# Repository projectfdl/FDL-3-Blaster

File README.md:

# FDL-3-Blaster

Welcome to the FDL-3 blaster repository

## This project is licensed under the terms of the Creative Commons Non-Commercial Attribution Share Alike 4.0 license
Print it, tweak it, share it and if you do and give us props. Please don't sell it without Project FDL permission.

<br>
<br>

# Operating your FDL-3

## Settings (Applicable to full auto tail, firmware version 1.05)

**Speed**<br>
Value: 0 - 100 : Default: 50<br>
Speed or power setting used to adjust the velocity the blaster fires darts.<br><br>

**ROF (Rate of Fire)**<br>
Value: 0 - 100 : Default: 100<br>
Rate of fire setting to adjust time between each dart fired when in burst or full auto.<br><br>

**Burst**<br>
Value: 1, 2, 3, F : Default: 1<br>
Number of darts fired per single trigger pull. F (full auto) will continue firing darts until you release the trigger.<br><br>

**MinSpin (Minimum Spinup)**<br>
Value: 120 - 500 : Default: 220<br>
Time in milliseconds for motors to spinup between trigger pull and firing dart when speed set to 0.<br><br>

**MaxSpin (Maximum Spinup)**<br>
Value: 150 - 500 : Default: 200<br>
Time in milliseconds for motors to spinup between trigger pull and firing dart when speed set to 100.
Note: MinSpin and MaxSpin together create a range of spinup time. When speed is set to 50, spinup time is half way between MinSpin and MaxSpin. Eg. MinSpin = 200, MaxSpin = 300, Speed = 50. Actual spinup time = 250. Speed = 75. Actual spinup time = 275.<br><br>

**Fire Mode**<br>
Value: SAFE, ABIDE, AUTO, CACHE : Default: ABIDE<br>
Setting for how the blaster reacts to a trigger pull prior to firing a dart.<br>
- Safe: safety mode. Blaster will beep and not fire dart.
- Abide: Trigger abide. Blaster will only fire a dart if trigger is held down for the full spinup duration. If trigger is released prior to the completion of spinupt time, the blaster will not fire.
- Auto: Blaster will fire dart automatically. If trigger is released prior to the completion of spinup time, the blaster will continue it's fire cycle and proceed to fire all darts set by the burst setting.
- Cache: Cached mode. The blaster will "cache" the number of trigger pulls during the spinup duration. If you are able to pull the trigger three times during spinup, the blaster will fire three darts. Twice, two darts. Once, one dart.<br><br>

**Spindown**<br>
Value: 7 - 18 : Default: 14<br>
Rate at which the blasters motors wind down or "spindown" to a stop. Lower is faster. Higher is slower. The value is technically equal to the time in milliseconds to lower the speed of the blaster by a single increment.<br><br>

**Idle (Idle Time)**<br>
Value: 0 - 10 : Default: 0<br>
After the end of a fire cycle the motors will spin at a slow idle speed for this number of seconds. This allows the motors to spinup faster than if they were to start from a dead stop. Setting this to 0 will disable the feature. Note: if the trigger is held down at the end of a fire cycle, the motors will run at this idle speed until trigger is released.<br><br>

**Load**<br>
Load user preset 1, 2, 3 or back out of menu.<br><br>

**Save**<br>
Save current blaster settings to one of three user preset slots which can be recalled later by the load menu or user buttons on the side of the blaster. Note: only settings prior before the Load menu item are stored in presets. Speed, ROF, Burst, MinSpin, MaxSpin, FireMode, Spindown and Idle.<br><br>

**MinSpd (Minimum Speed)**<br>
Value: 0 - 100 : Default: 0<br>
Determines the minimum speed value that may be set by the speed setting. Eg. if set to 25, the speed gauge will not go lower than 25.<br><br>

**MaxSpd (Maximum Speed)**<br>
Value: 0 - 100 : Default: 100<br>
Determines the maximum speed value that may be set by the speed setting. Eg. if set to 80, the speed gauge will not go higher than 80. Recalled presets with higher speed values will default to this setting. The last value this setting was set to prior to powering off the blaster can be locked by flipping the red speed lock switch located on next to the screen on the board in the rear of the blaster. The rear cap piece must be removed to access this switch. This value cannot be altered while the blaster speed lock is enabled.<br><br>

**BtnMode (Button Mode)**<br>
Value: PRESET, SPEED, ROF, BURST : Default: BURST<br>
Determines what the three user quick buttons on the side of the blaster do. These buttons must be briefly held down for action to take place.<br>
- Preset: Loads user preset. Front button loads preset 1. Rear button closed to user loads preset 3.
- Speed: Sets blaster speed. From front to rear button. 50, 75, 100
- ROF: Set blaster rate of fire. From front to rear button. 50, 75, 100
- Burst: Sets blaster burst count. From front to rear button. 1, 2, F<br><br>

**BrkAgr (Braking Aggression)**<br>
Value: 3 - 20 : Default: 16<br>
Determines how aggressively the pusher brakes prior to reaching a stop at the rear of its cycle. Setting lower may produce a more responsive cycle but may leave the pusher extended at the end of the cycle. Setting higher may resolve issues with a pusher that does not stop properly at the rear of its cycle. This setting should rarely need to change.<br><br>

**ULock (User Lock)**<br>
Enable complete blaster lockout by setting a user defined sequence of quick button presses. Blaster will not function once lock is set and may be unlocked by reentering the defined sequence. Note: do not forget your code. While it is possible to reset your blaster, the method of doing so is not described in this document.<br><br>

**Bright (Brightness)**<br>
Value: 0 - 100 : Default: 100<br>
Sets the brightness of the oled display. This is a very subtle change in a high light environment but more obvious in darker surroundings.<br><br>

**Sound**<br>
Value: OFF, ON : Default: ON<br>
Enables or disables audible beeping while navigating menus, loading presets etc.<br><br>

**BatOff (Battery Offset)**<br>
Value: -5 - 5 : Default: 0<br>
Offsets the read battery voltage in increments of 0.1 volts. This is only for use with legacy or self built blasters if a full 3s battery does not read 12.6 volts.<br><br>

**Info**<br>
Displays current firmware version.<br><br>

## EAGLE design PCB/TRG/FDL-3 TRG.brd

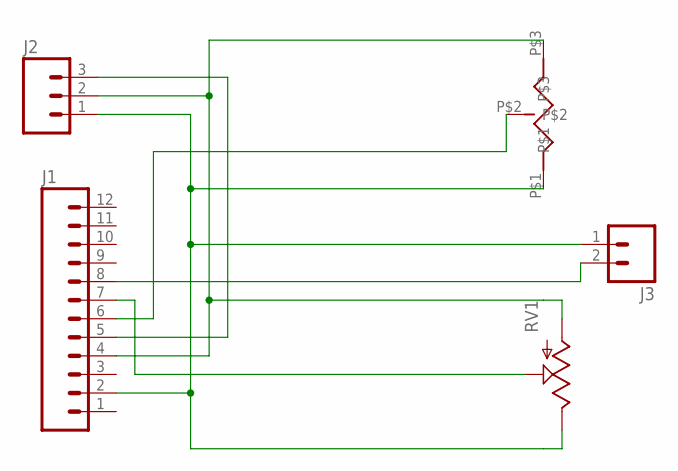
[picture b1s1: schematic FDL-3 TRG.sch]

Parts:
J1: M12LONGPADS; 1X12_LONGPADS
J2: M03LONGPADS; 1X03_LONGPADS
J3: M02PTH3; 1X02_LONGPADS
RV1: POTTRIM; TRIM_POT
U$1: THRUHOLEPOT

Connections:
unnamed: J1.2, J2.1, J3.1, RV1.2 (E), U$1.P$1
unnamed: J1.4, J2.2, RV1.3 (A), U$1.P$3
unnamed: J1.5, J2.3
unnamed: J1.6, U$1.P$2
unnamed: J1.7, RV1.1 (S)
unnamed: J1.8, J3.2

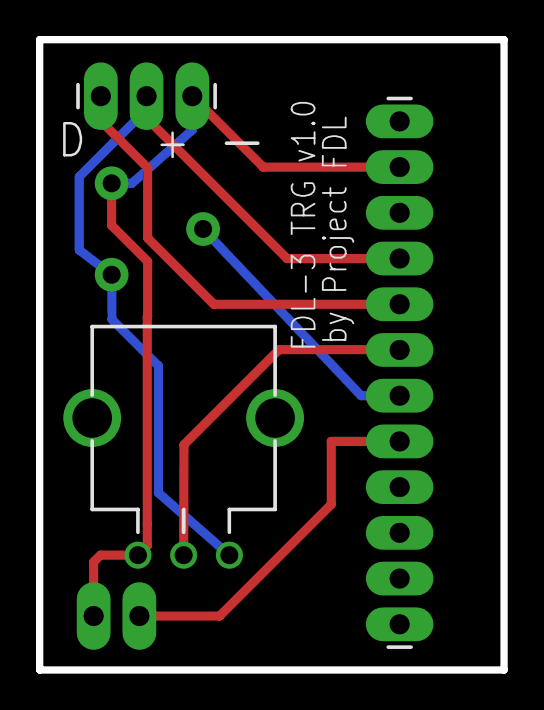
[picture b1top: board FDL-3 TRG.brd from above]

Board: 2 copper layers, 25.8 x 35.0 mm, 5 parts (0 on the bottom side), 6 nets.

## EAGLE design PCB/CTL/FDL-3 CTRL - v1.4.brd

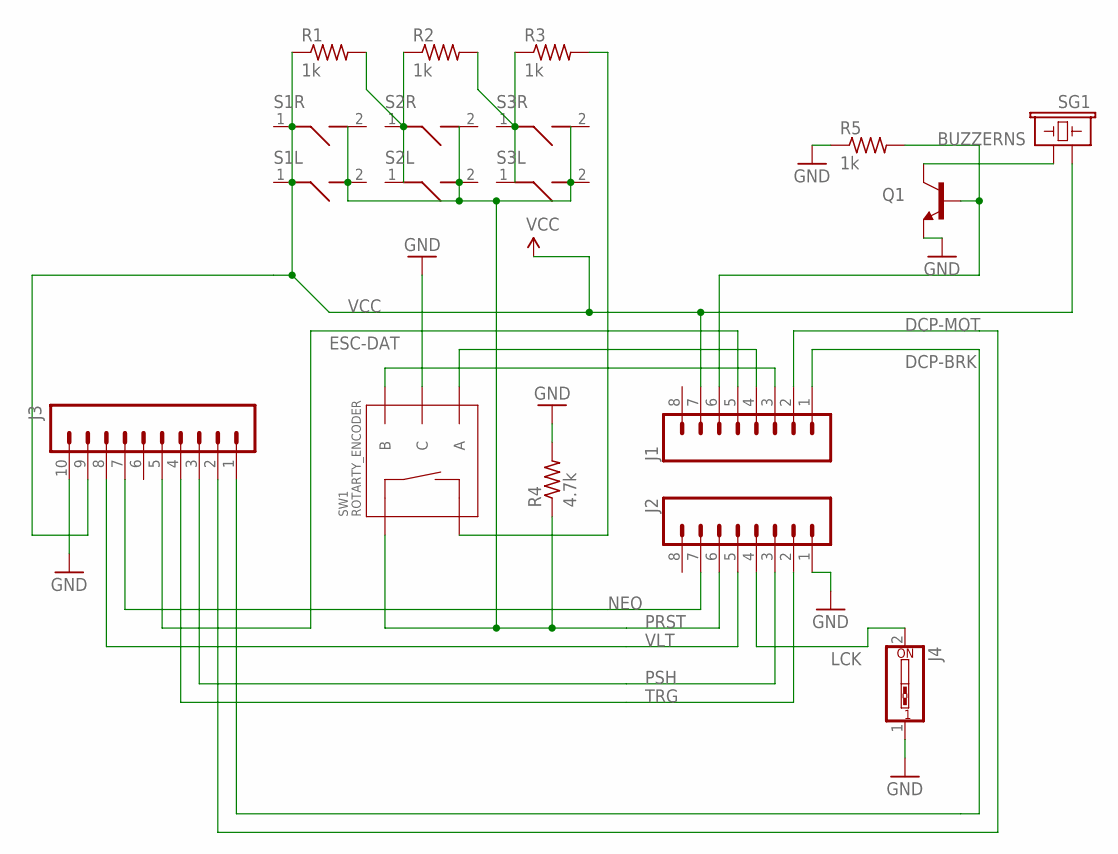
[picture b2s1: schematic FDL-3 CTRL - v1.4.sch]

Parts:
J1, J2: M08SILK_FEMALE_PTH; 1X08
J3: M10SILK_FEMALE_PTH; 1X10
J4: SW_DIP-1; EDG-01
Q1: TRANSISTOR_NPNBC547; TO-92-AMMO
R1, R2, R3, R5: 1k; 0204/5
R4: 4.7k; 0204/5
S1L, S1R, S2L, S2R, S3L, S3R: RGTANGTCTBTN
SG1: BUZZERNS; BUZZER-12MM-NS
SW1: ROTARTY_ENCODER; ROTARY_ENC_PLAIN

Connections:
DCP-BRK: J1.1, J3.1
DCP-MOT: J1.2, J3.2
ESC-DAT: J1.5, J3.5
GND: J2.1, J3.10, J4.1, Q1.3 (E), R4.2, R5.1, SW1.C
LCK: J2.4, J4.2
unnamed: R1.2, R2.1, S2L.1, S2R.1
unnamed: R2.2, R3.1, S3L.1, S3R.1
unnamed: R3.2, SW1.SW-
unnamed: Q1.1 (C), SG1.- (2)
unnamed: J1.4, SW1.A
unnamed: J1.3, SW1.B
unnamed: J1.6, Q1.2 (B), R5.2
NEO: J2.7, J3.7
PRST: J2.6, R4.1, S1L.2, S1R.2, S2L.2, S2R.2, S3L.2, S3R.2, SW1.SW+
PSH: J2.3, J3.3
TRG: J2.2, J3.4
VCC: J1.7, J3.9, R1.1, S1L.1, S1R.1, SG1.+ (1)
VLT: J2.5, J3.8

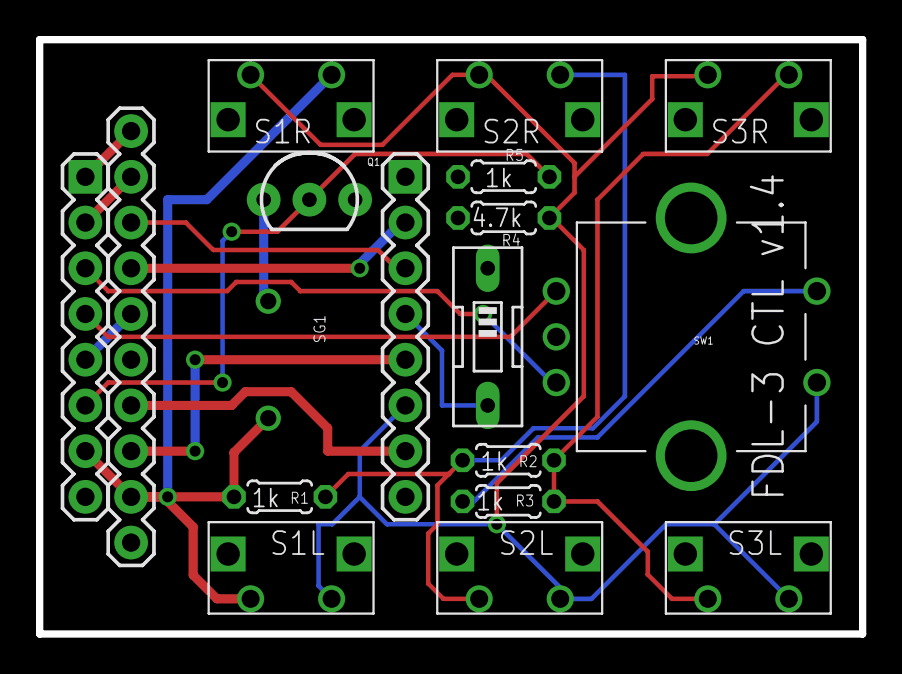
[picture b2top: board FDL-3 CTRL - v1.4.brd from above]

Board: 2 copper layers, 45.7 x 33.0 mm, 18 parts (0 on the bottom side), 18 nets.

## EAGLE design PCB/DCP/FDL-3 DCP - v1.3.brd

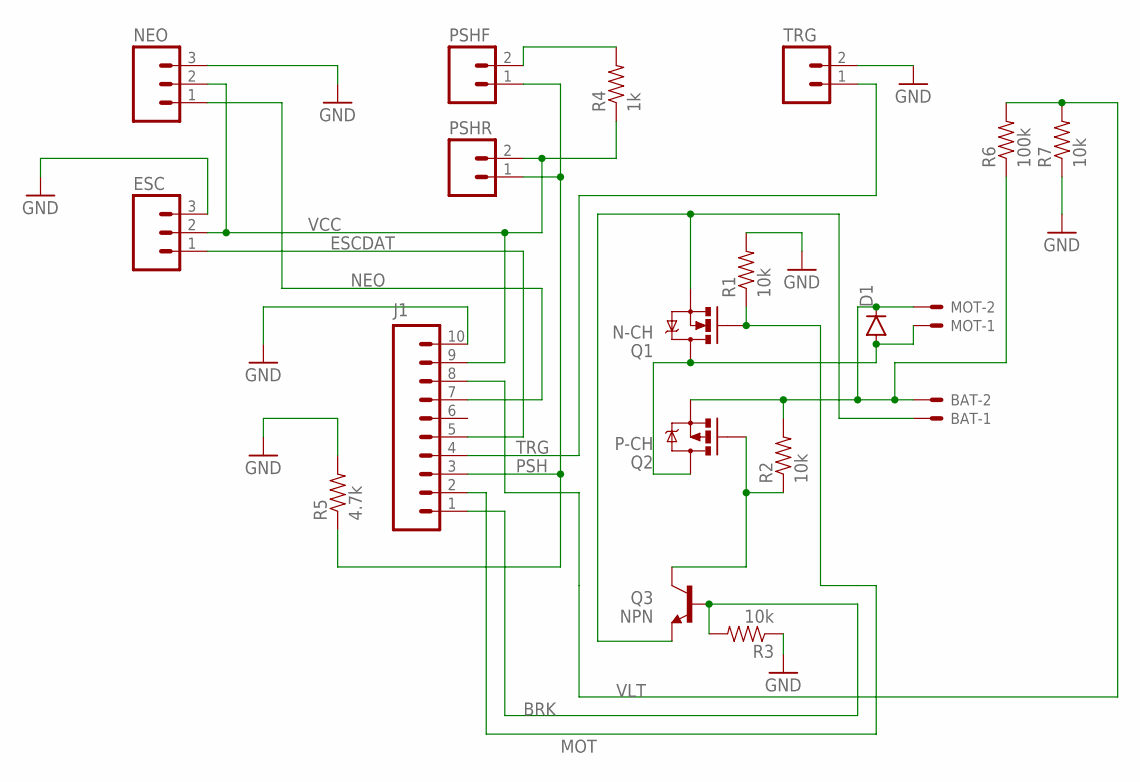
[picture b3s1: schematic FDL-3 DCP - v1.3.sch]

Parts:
BAT: JST-XH-02-PIN-LONG-PAD; JST-XH-02-PACKAGE-LONG-PAD
D1: DIODEPTH; DIODE-1N4001
ESC: M03PTH; 1X03
J1: M10SILK_FEMALE_PTH; 1X10
MOT: JST-XH-02-PIN-LONG-PAD; JST-XH-02-PACKAGE-LONG-PAD
NEO: M03PTH; 1X03
PSHF: M02PTH; 1X02
PSHR: M02PTH; 1X02
Q1: N-CH; TO220V
Q2: P-CH; TO220V
Q3: NPN; TO-92
R1, R2, R3, R7: 10k; AXIAL-0.3EZ
R4: 1k; AXIAL-0.3EZ
R5: 4.7k; AXIAL-0.3EZ
R6: 100k; AXIAL-0.3EZ
TRG: M02PTH; 1X02

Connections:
BRK: J1.1, Q3.2 (B), R3.P$2 (2)
ESCDAT: ESC.1, J1.5
GND: BAT.1, ESC.3, J1.10, NEO.3, Q1.3 (S), Q3.1 (E), R1.P$2 (2), R3.P$1 (1), R5.P$2 (2), R7.P$1 (1), TRG.2
MOT: J1.2, Q1.1 (G), R1.P$1 (1)
unnamed: Q2.1 (G), Q3.3 (C), R2.P$1 (1)
unnamed: BAT.2, D1.C, MOT.2, Q2.3 (S), R2.P$2 (2), R6.P$1 (1)
unnamed: D1.A, MOT.1, Q1.2 (D), Q2.2 (D)
unnamed: PSHF.2, R4.P$2 (2)
NEO: J1.7, NEO.1
PSH: J1.3, PSHF.1, PSHR.1, R5.P$1 (1)
TRG: J1.4, TRG.1
VCC: ESC.2, J1.9, NEO.2, PSHR.2, R4.P$1 (1)
VLT: J1.8, R6.P$2 (2), R7.P$2 (2)

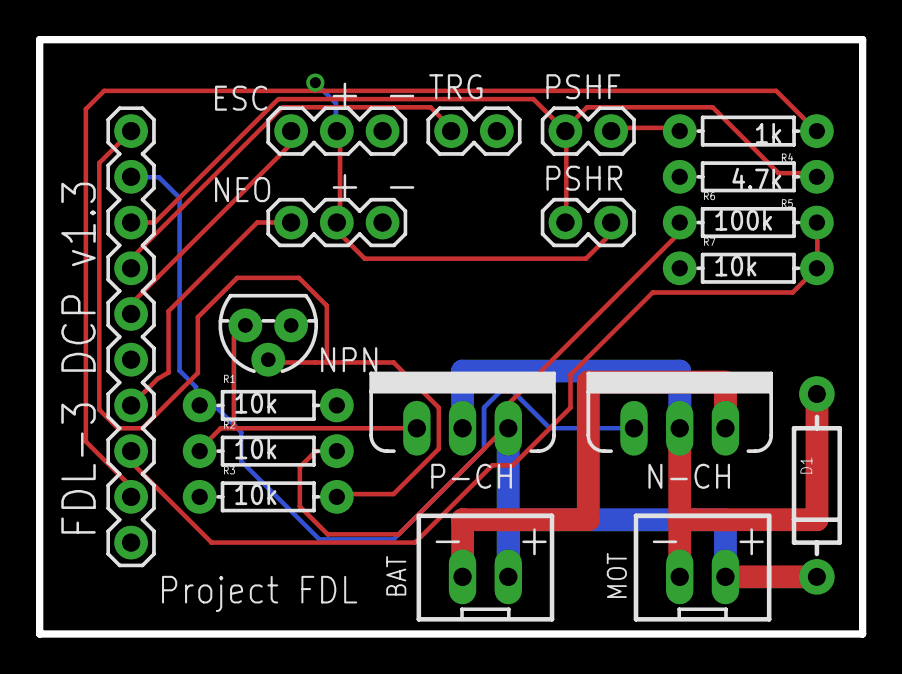
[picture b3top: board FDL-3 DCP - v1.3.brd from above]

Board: 2 copper layers, 45.7 x 33.0 mm, 19 parts (0 on the bottom side), 13 nets.

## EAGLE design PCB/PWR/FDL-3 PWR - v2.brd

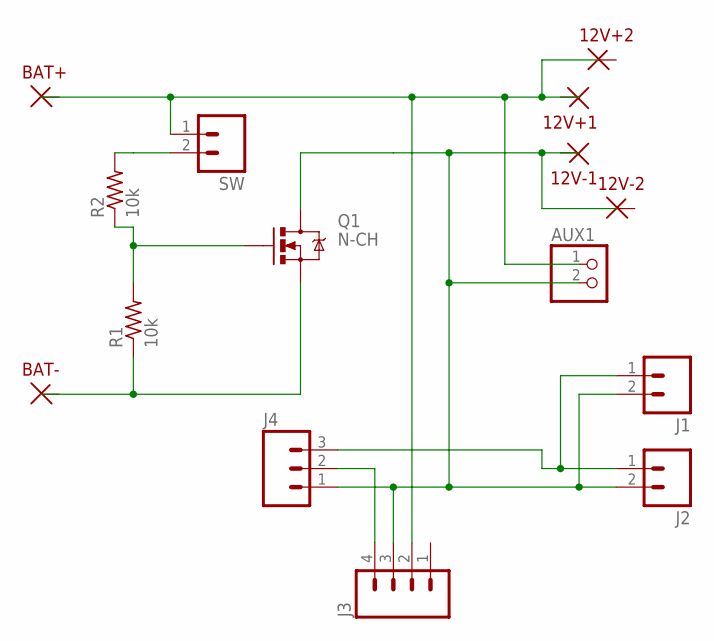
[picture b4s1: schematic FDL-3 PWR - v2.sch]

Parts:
12V+1, 12V+2, 12V-1, 12V-2: PWRPAD18
AUX1: PINHD-1X2; 1X02
BAT+: PWRPAD16
BAT-: PWRPAD16
J1, J2: M02PTH; 1X02
J3: M04PTH; 1X04
J4: M03PTH; 1X03
Q1: N-CH; TO220V
R1, R2: 10k; 0204/5
SW: M02PTH; 1X02

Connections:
unnamed: R2.2, SW.2
unnamed: J3.4, J4.2
unnamed: Q1.1 (G), R1.2, R2.1
unnamed: BAT-.P$1, Q1.3 (S), R1.1
unnamed: J1.1, J2.1, J4.3
unnamed: 12V+1.P$1, 12V+2.P$1, AUX1.1, BAT+.P$1, J3.2, SW.1
unnamed: 12V-1.P$1, 12V-2.P$1, AUX1.2, J1.2, J2.2, J3.3, J4.1, Q1.2 (D)

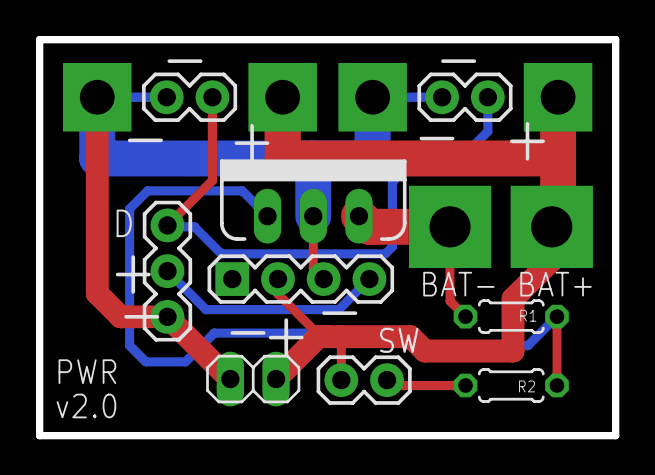
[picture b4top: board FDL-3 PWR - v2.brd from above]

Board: 2 copper layers, 32.0 x 22.0 mm, 15 parts (0 on the bottom side), 7 nets.

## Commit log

2018-10-04 initial push
2018-10-04 Added caution message to readme
2019-02-05 first stl push
2019-02-07 Firmware and PCB push
2019-02-07 Print orienting nose full stls
2019-02-07 Print oriented tail auto stls
2019-02-07 cad files initial push
2019-02-07 print oriented tail semi stls
2019-02-18 adding knob
2019-02-28 Updating for print orientation
2019-02-28 Updating print orientation
2019-02-28 Adding ESC firmware
2019-03-03 Fixing mag release pivot oddities
2019-03-03 Rearranging mag release components
2019-03-08 adding 1.03 firmware hex file
2019-03-22 Part tweaks and print orientation
2019-03-29 Adding top rail to forty nose
2019-04-06 BOM upload
2019-04-06 Switch to xslx
2019-04-19 Mag fit tweaks
2019-04-24 Create dfsdf
2019-05-02 Adding TRG PCB
2019-05-07 Adding HIR nose files
2019-07-05 Adding flywheel readme
2019-07-05 readme update
2019-07-22 Adding dwell pusher for testing
2019-07-22 cleanup
2019-07-28 Updating flywheels and mock motors to lumenier versions
2019-08-31 Adding pivot file to forty fose stls
2019-08-31 Adding initial 1.04 firmware files
2019-09-21 Adding 2206 flywheel
2019-09-25 Adding logo to shorty blaster stand
2019-11-09 Fixed BOM links
2019-11-24 Add printing readme
2019-11-30 Adding witing diagram
2019-12-05 Updating resistor quantities, adding pdfs
2019-12-08 Updating main readme to remove branch note
2019-12-08 Updating trigger with small chamfer
2019-12-08 removing dwell pusher
2020-01-02 Adding Robo Stock
2020-01-03 Orienting for print
2020-04-18 Replace dwg cad files with f3d and step
2020-05-02 Adding crux wheels updating pusher componenets for no drill and tap
2020-05-02 Orienting pusher housing cap for print
2020-05-10 Adding initial operating instructions to readme
2020-05-10 Adding line breaks to readme
2020-06-11 Add v1.05 firmware
2020-06-11 Add Crux ESC firmware ini
2020-08-18 Changed Libraries to Adafruit OLED and deactivated all Microview specific functionality to get a baseproject
2020-08-18 Added VSCode Files
2020-08-18 Changed Splash Text
2020-08-18 Renamed uView to oled and fixed SplashScreen
2020-08-18 Changed RenderHelper Functions
2020-08-18 Added Arduino GFX Library
2020-08-19 Adjusted renderMenu and renderGauge
2020-08-22 Tried to pinpint Stack Error
2020-08-22 Added Modified STL File for Arduino Pro Micro and OLED
2020-08-22 Added Adaptor to use generic microswitches (as in Endstops) as Trigger
2020-09-03 Added Flywheel for EMAX HIR
2020-09-03 Reverted firmware to original state
2020-09-03 Reverted Pin changes
2020-09-03 Removed .vscode folder
2020-09-03 Reverted readme.md
2021-03-11 Add HIR blaster stand stl

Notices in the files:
parts and their libraries:
SparkFun-Connectors: Licensing: Creative Commons ShareAlike 4.0 International - https://creativecommons.org/licenses/by-sa/4.0
